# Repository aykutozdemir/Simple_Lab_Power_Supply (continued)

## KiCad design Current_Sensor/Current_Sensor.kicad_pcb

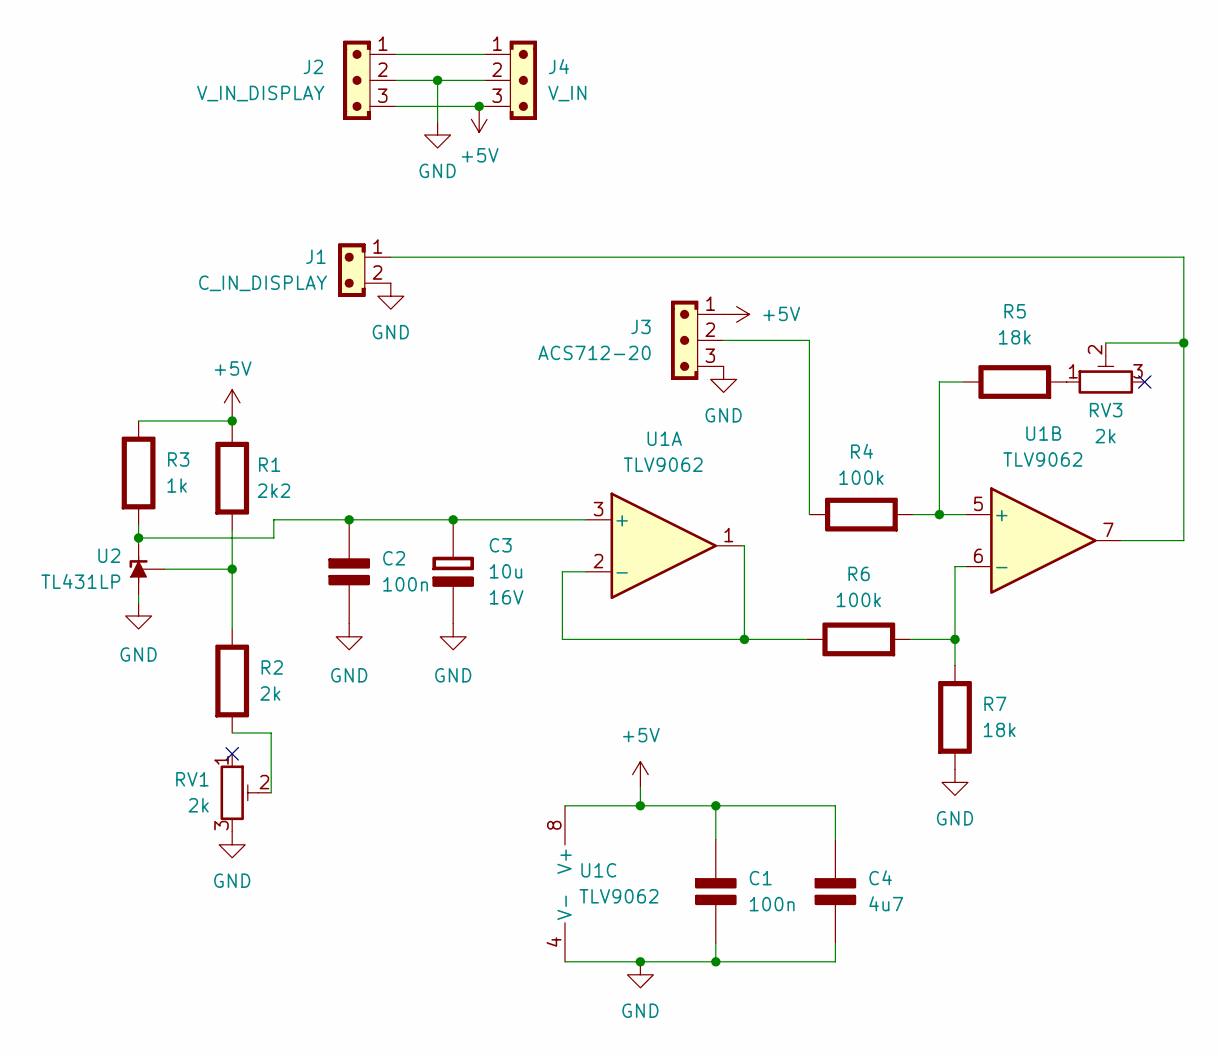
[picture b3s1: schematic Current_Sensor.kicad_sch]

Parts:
C1, C2: 100n; C_Disc_D5.0mm_W2.5mm_P5.00mm; Rating 50V
C3: 10u; CP_Radial_Tantal_D4.5mm_P5.00mm; Rating 16V
C4: 4u7; C_Disc_D5.0mm_W2.5mm_P5.00mm; Rating 50V
J1: C_IN_DISPLAY; PinHeader_1x02_P2.54mm_Vertical
J2: V_IN_DISPLAY; PinHeader_1x03_P2.54mm_Vertical
J3: ACS712-20; PinHeader_1x03_P2.54mm_Vertical
J4: V_IN; JST_XH_B3B-XH-A_1x03_P2.50mm_Vertical
R1: 2k2; R_Axial_DIN0204_L3.6mm_D1.6mm_P7.62mm_Horizontal
R2: 2k; R_Axial_DIN0204_L3.6mm_D1.6mm_P7.62mm_Horizontal
R3: 1k; R_Axial_DIN0204_L3.6mm_D1.6mm_P7.62mm_Horizontal
R4: 100k; R_Axial_DIN0204_L3.6mm_D1.6mm_P7.62mm_Horizontal; Rating %1
R5, R7: 18k; R_Axial_DIN0204_L3.6mm_D1.6mm_P7.62mm_Horizontal; Rating %1
R6: 100k; R_Axial_DIN0309_L9.0mm_D3.2mm_P15.24mm_Horizontal; Rating %1
RV1, RV3: 2k; Potentiometer_Bourns_3296W_Vertical
U1: TLV9062; DIP-8_W7.62mm_Socket
U2: TL431LP; TO-92_Inline

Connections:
+5V: C1.1 (+), C4.1 (+), J2.3, J3.1, J4.3, R1.1 (+), R3.1 (+), U1.8 (V+)
GND: C1.2 (-), C2.2 (-), C3.2 (-), C4.2 (-), J1.2, J2.2, J3.3, J4.2, R7.2 (-), RV1.3, U1.4 (V-), U2.2 (A)
unnamed: C2.1 (+), C3.1 (+), R3.2 (-), U1.3 (+), U2.3 (K)
unnamed: J1.1, RV3.2, U1.7
unnamed: J2.1, J4.1
unnamed: R1.2 (-), R2.1 (+), U2.1 (REF)
unnamed: R2.2 (-), RV1.2
unnamed: J3.2, R4.1 (+)
unnamed: R4.2 (-), R5.1 (+), U1.5 (+)
unnamed: R5.2 (-), RV3.1
unnamed: R6.1 (+), U1.1, U1.2 (-)
unnamed: R6.2 (-), R7.1 (+), U1.6 (-)

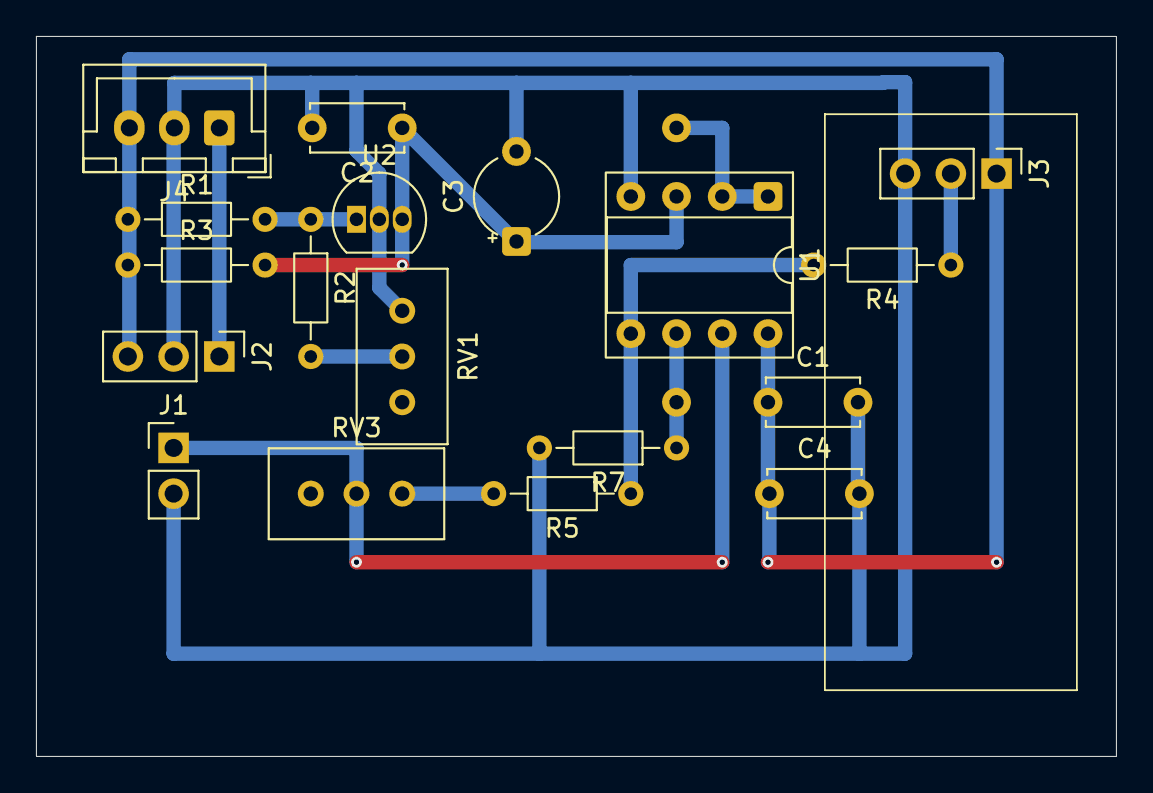
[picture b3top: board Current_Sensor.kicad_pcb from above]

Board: 2 copper layers, 60.0 x 40.0 mm, 19 parts (1 on the bottom side), 12 nets.

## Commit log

2025-09-07 Circuit design
2025-09-07 3D design
2025-09-07 Undervoltage protection fixed for adj ch
2025-09-07 svg exports
2025-09-07 3D design completed
